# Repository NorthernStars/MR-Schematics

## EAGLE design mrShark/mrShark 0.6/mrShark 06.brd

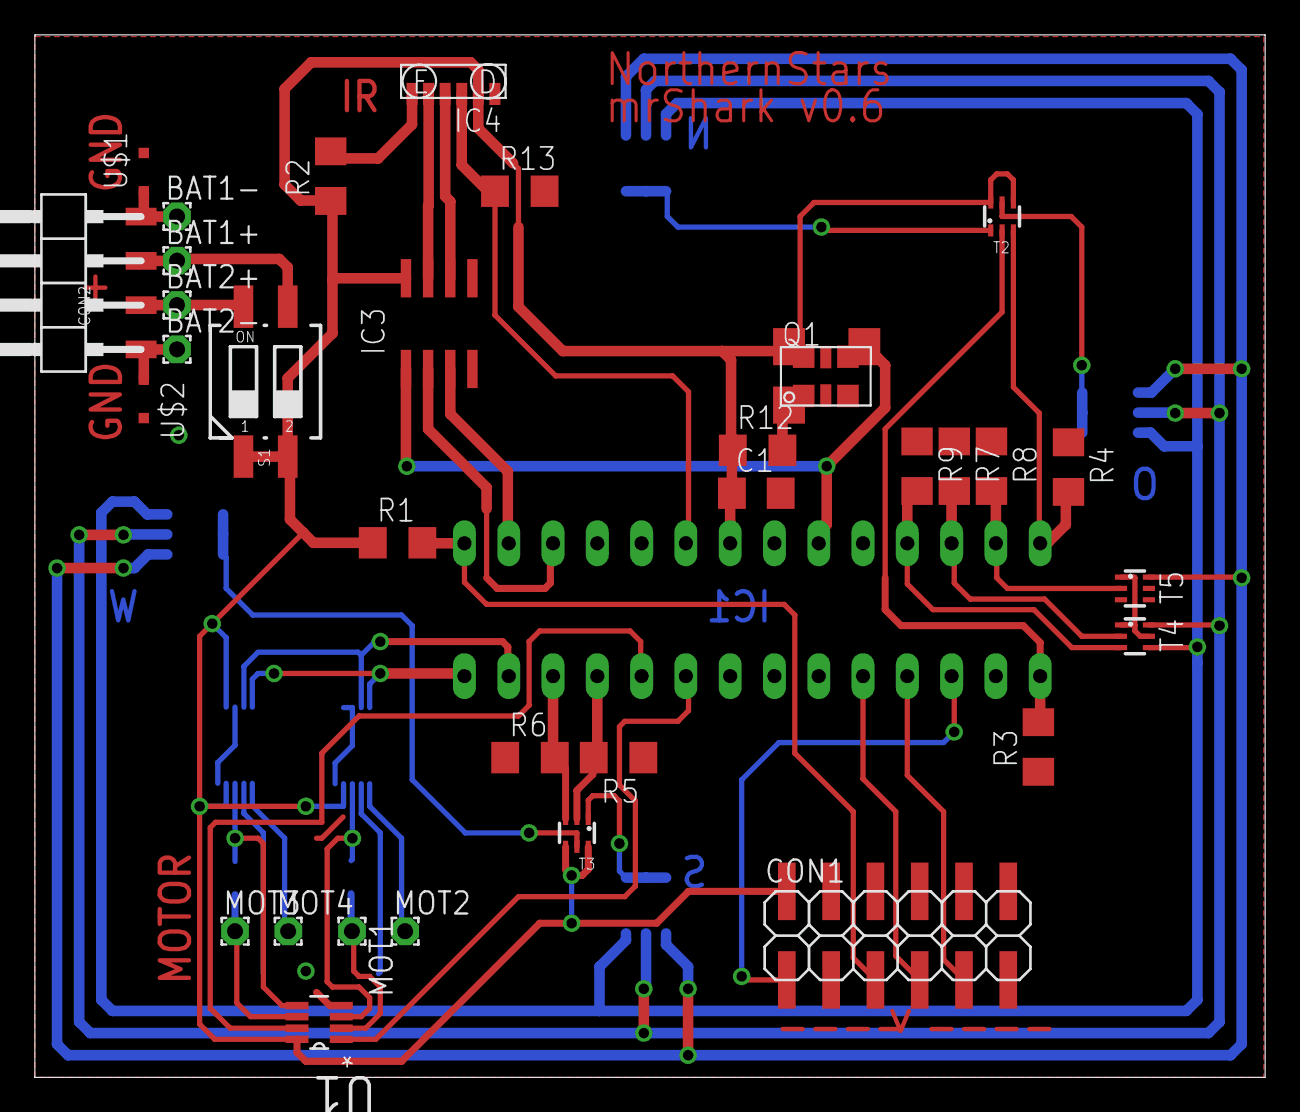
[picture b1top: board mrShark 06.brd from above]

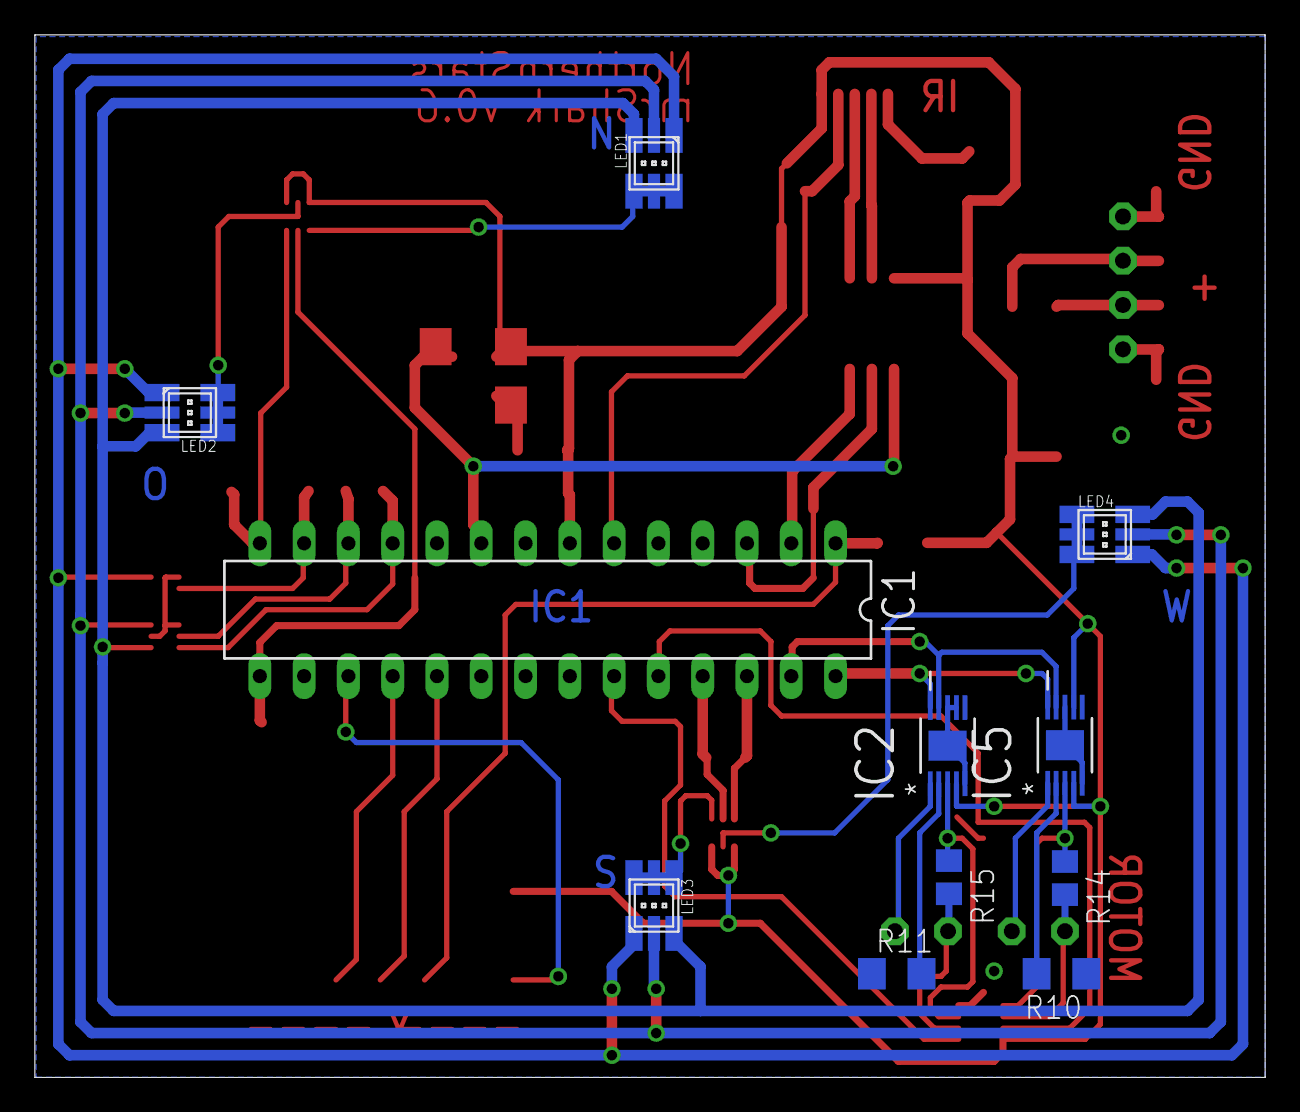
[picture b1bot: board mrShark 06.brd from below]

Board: 2 copper layers, 70.6 x 59.8 mm, 44 parts (11 on the bottom side), 44 nets.

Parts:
BAT1+, BAT1-, BAT2+, BAT2-: 1,6/0,9
C1: 100n; C1206
CON1: 2X06SMD
CON2: 1X04SMD/90
IC1: MEGA48/88/168-PU; DIL28-3
IC2, IC5: DRV8830DGQRMSOP; SOP65P640X110-15N
IC3: TIR1000PSR; SO-08
IC4: TFBS4711TR1; TFBS4711
LED1, LED2, LED3, LED4: ASMT-YTD2-0BB02; PLCC6K
MOT1, MOT2, MOT3, MOT4: 1,6/0,9
Q1: ASFLM1-1.8432MHZ-L-C-T; HC536
R1, R3, R4, R5, R6, R7, R8, R9, R12, R13: 1k; R1206
R2: 27R; R1206
R10, R11: 0.95R; R1206
R14, R15: 0R2; R0805
S1: MCEMR-02-T; CTS-219-02
T2, T3: UMX3NTR; SOT363_INFINEON
T4, T5: UMX3NTR-SOT363; SOT363_INFINEON
U1: OPA2348AIDCNTG4; SOT65P280X145-8N
U$1, U$2: PMEG2010EAR; SOD323-R

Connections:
BAT1+: BAT1+.1, CON2.3, S1.3
BAT1-: BAT1-.1, CON2.4, U$1.C
BAT2+: BAT2+.1, CON2.2, S1.4
BAT2-: BAT2-.1, CON2.1, U$2.C
CLK: IC1.9, IC3.1, Q1.3
COLOR_B: LED1.1, LED2.1, LED3.1, LED4.1, T5.6
COLOR_G: LED1.2, LED2.2, LED3.2, LED4.2, T4.6
COLOR_R: LED1.3, LED2.3, LED3.3, LED4.3, T4.4
GND: C1.2, CON1.4, CON1.6, CON1.8, CON1.10, IC1.8, IC1.22, IC2.5, IC2.7, IC2.8, IC2.11, IC3.4, IC3.5, IC4.6, IC5.5, IC5.8, IC5.11, Q1.2, R3.1, R4.1, R5.1, R6.1, R7.1, R8.1, R9.1, R10.1, R11.1, R13.2, T4.1, T4.5, T5.1, U1.4, U$1.A, U$2.A
IRDA: IC4.1, R2.2
IR_SD: IC1.6, IC4.4, R13.1
ISENS_MOTL: IC1.23, U1.1
ISENS_MOTR: IC1.24, U1.7
LED1: IC1.15, R3.2, T2.2
LED1+: LED1.4, LED1.5, LED1.6, T2.1
LED2: IC1.14, R4.2, T2.3
LED2+: LED2.4, LED2.5, LED2.6, T2.5
LED3: IC1.25, R5.2, T3.2
LED3+: LED3.4, LED3.5, LED3.6, T3.1
LED4: IC1.26, R6.2, T3.3
LED4+: LED4.4, LED4.5, LED4.6, T3.5
LED_B: IC1.13, R8.2, T5.2
LED_G: IC1.12, R7.2, T4.2
LED_R: IC1.11, R9.2, T4.3
MISO: CON1.9, IC1.18
MOSI: CON1.1, IC1.17
unnamed: IC5.1, MOT4.1
unnamed: Q1.1, R12.2
unnamed: IC5.2, R10.2
unnamed: IC2.2, R11.2
unnamed: IC2.1, MOT2.1
RESET: CON1.5, IC1.1, R1.2
RXD: IC1.2, IC3.3
RXIR: IC3.6, IC4.3
SCK: CON1.7, IC1.19
SCL: IC1.28, IC2.10, IC5.10
SDA: IC1.27, IC2.9, IC5.9
SENS_MOTL1: IC2.3, R15.1, U1.3
SENS_MOTL2: MOT1.1, R15.2, U1.2
SENS_MOTR1: IC5.3, R14.1, U1.5
SENS_MOTR2: MOT3.1, R14.2, U1.6
TXD: IC1.3, IC3.2
TXIR: IC3.7, IC4.2
VCC: C1.1, CON1.2, IC1.7, IC1.20, IC1.21, IC2.4, IC3.8, IC4.5, IC5.4, IC5.7, Q1.4, R1.1, R2.1, R12.1, S1.1, S1.2, T2.4, T2.6, T3.4, T3.6, U1.8

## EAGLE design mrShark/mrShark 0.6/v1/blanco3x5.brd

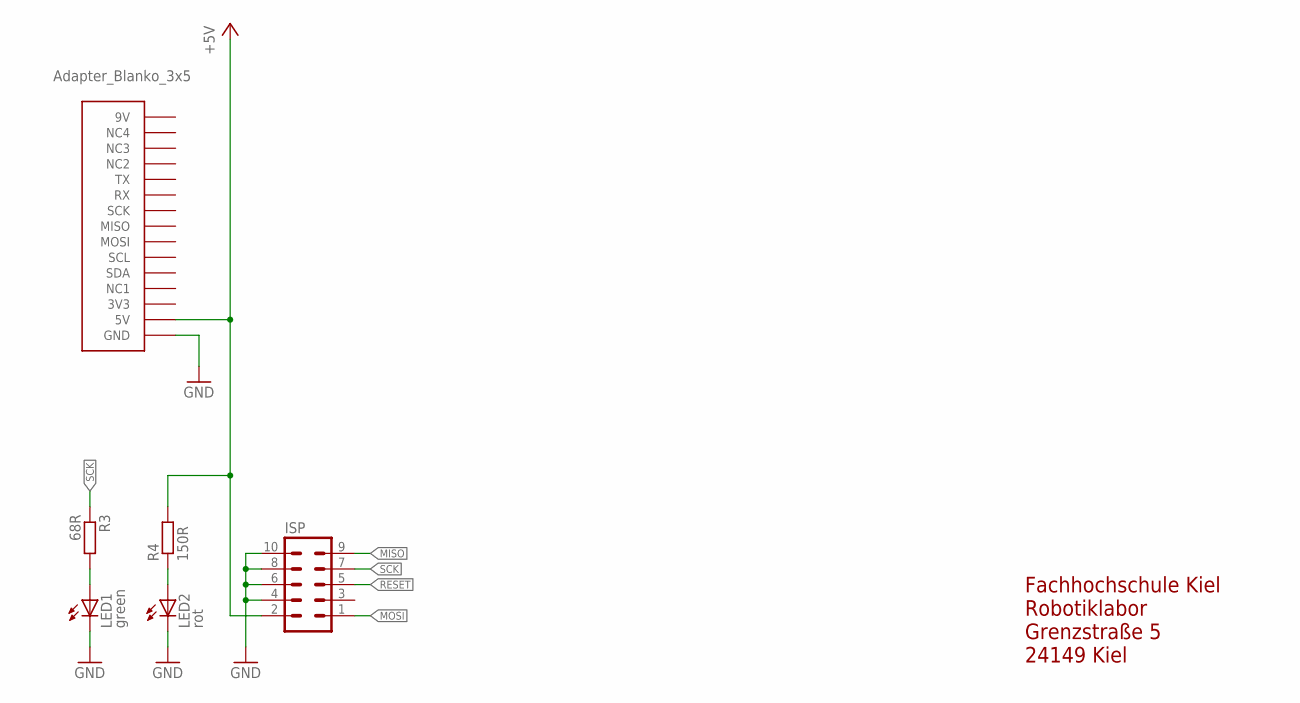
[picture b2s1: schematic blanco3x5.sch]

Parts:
ISP: ML10L
LED1: green; CHIP-LED0805
LED2: rot; CHIP-LED0805
R3: 68R; R0805W
R4: 150R; R0805W
U$1: ADAPTER_BLANKO_3X5B2; ADAPTER_BLANKO_3X5_B2

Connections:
+5V: ISP.2, R4.2, U$1.5V, U$1.5V_1 (5V)
GND: ISP.4, ISP.6, ISP.8, ISP.10, LED1.C, LED2.C, U$1.GND, U$1.GND1 (GND), U$1.GND2 (GND), U$1.GND3 (GND)
MISO: ISP.9
MOSI: ISP.1
unnamed: LED1.A, R3.2
unnamed: LED2.A, R4.1
RESET: ISP.5
SCK: ISP.7, R3.1

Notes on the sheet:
Fachhochschule Kiel Robotiklabor Grenzstraße 5 24149 Kiel

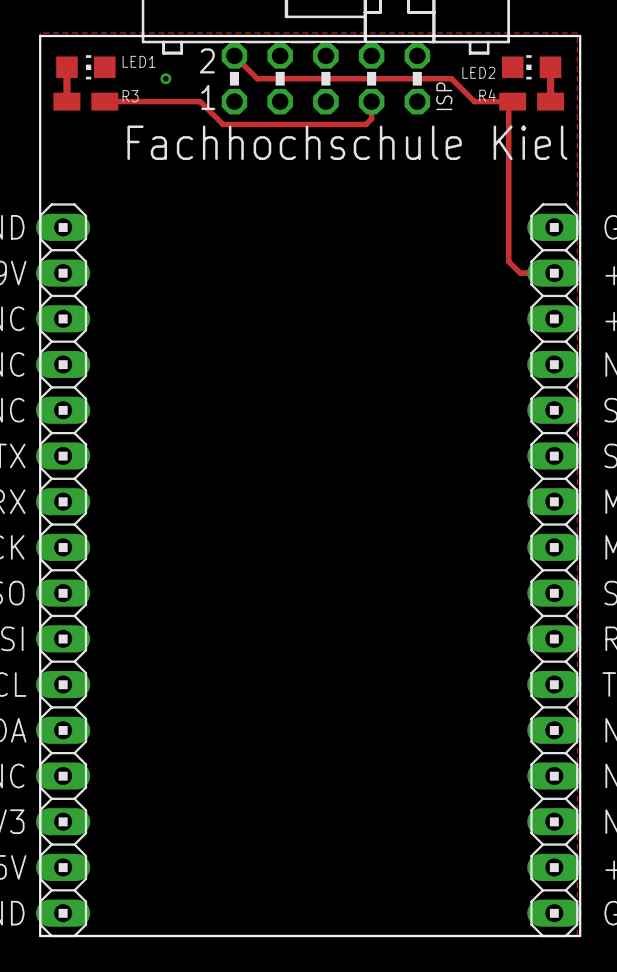
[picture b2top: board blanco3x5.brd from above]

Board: 2 copper layers, 30.0 x 50.0 mm, 6 parts (0 on the bottom side), 5 nets.

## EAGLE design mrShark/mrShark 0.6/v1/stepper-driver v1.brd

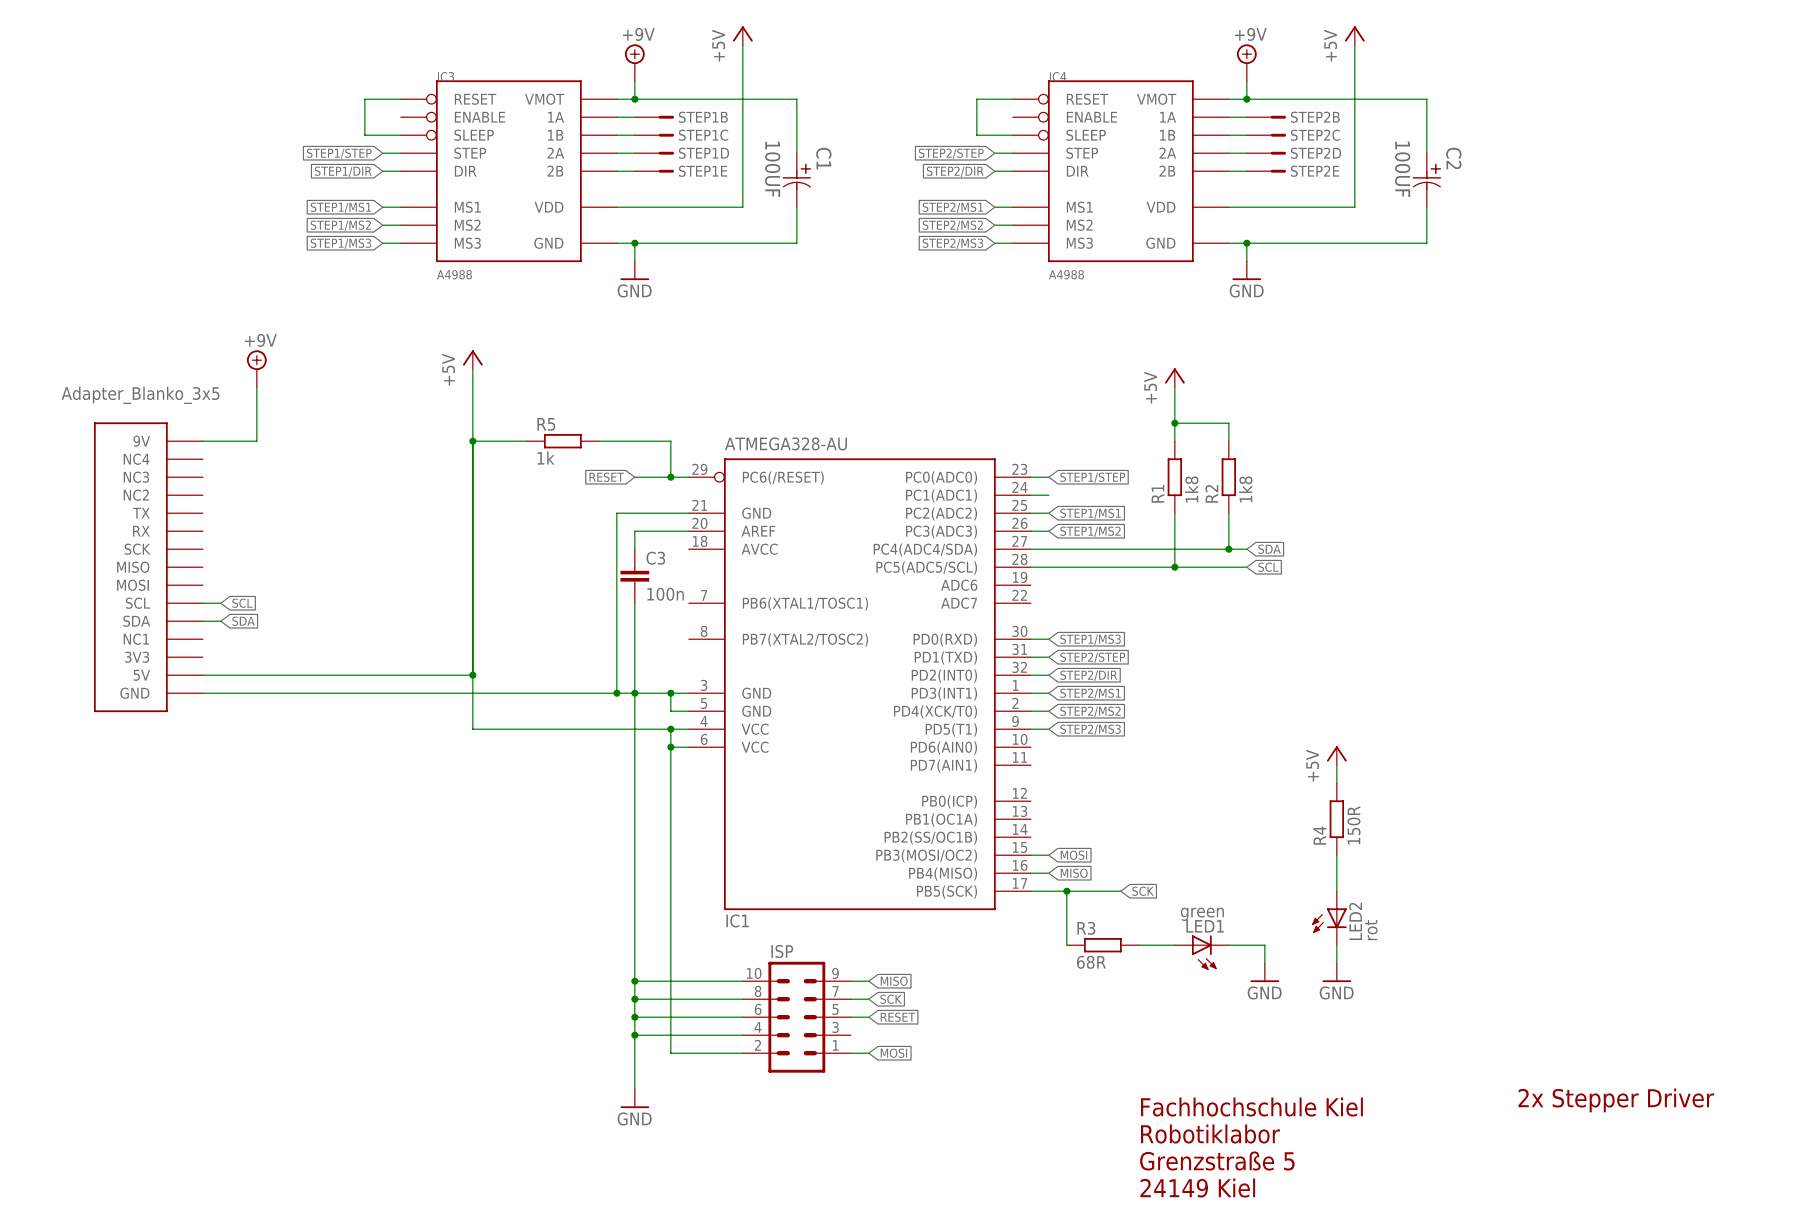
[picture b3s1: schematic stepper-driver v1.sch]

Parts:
ADAPTER: ADAPTER_BLANKO_3X5B2; ADAPTER_BLANKO_3X5_B2
C1, C2: 100UF; CAPAE660X610N
C3: 100n; C0805K
IC1: ATMEGA328-AU; TQFP32-08
IC3, IC4: A4988; A4988SHIELD-SMD
ISP: ML10L
LED1: green; CHIP-LED0805
LED2: rot; CHIP-LED0805
R1, R2: 1k8; R0805W
R3: 68R; R0805W
R4: 150R; R0805W
R5: 1k; R0805W
STEP1, STEP2: B5B-XH-A

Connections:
+5V: ADAPTER.5V, ADAPTER.5V_1 (5V), IC1.4 (VCC), IC1.6 (VCC), IC3.VDD, IC4.VDD, ISP.2, R1.2, R2.2, R4.2, R5.1
+9V: ADAPTER.9V, ADAPTER.9V_1 (9V), C1.1, C2.1, IC3.VMOT, IC4.VMOT
AVCC: IC1.18 (AVCC)
GND: ADAPTER.GND, ADAPTER.GND1 (GND), ADAPTER.GND2 (GND), ADAPTER.GND3 (GND), C1.2, C2.2, C3.2, IC1.3 (GND), IC1.5 (GND), IC1.21 (GND), IC3.GND, IC3.GND1 (GND), IC4.GND, IC4.GND1 (GND), ISP.4, ISP.6, ISP.8, ISP.10, LED1.C, LED2.C
MISO: IC1.16 (PB4(MISO)), ISP.9
MOSI: IC1.15 (PB3(MOSI/OC2)), ISP.1
unnamed: C3.1, IC1.20 (AREF)
unnamed: LED1.A, R3.2
unnamed: LED2.A, R4.1
unnamed: IC3.2B, STEP1.5
unnamed: IC3.2A, STEP1.4
unnamed: IC3.1B, STEP1.3
unnamed: IC3.1A, STEP1.2
unnamed: IC4.1A, STEP2.2
unnamed: IC4.1B, STEP2.3
unnamed: IC4.2A, STEP2.4
unnamed: IC4.2B, STEP2.5
RESET: IC1.29 (PC6(/RESET)), ISP.5, R5.2
SCK: IC1.17 (PB5(SCK)), ISP.7, R3.1
SCL: ADAPTER.SCL, ADAPTER.SCL_1 (SCL), IC1.28 (PC5(ADC5/SCL)), R1.1
SDA: ADAPTER.SDA, ADAPTER.SDA_1 (SDA), IC1.27 (PC4(ADC4/SDA)), R2.1
STEP1/DIR: IC1.24 (PC1(ADC1)), IC3.DIR
STEP1/MS1: IC1.25 (PC2(ADC2)), IC3.MS1
STEP1/MS2: IC1.26 (PC3(ADC3)), IC3.MS2
STEP1/MS3: IC1.30 (PD0(RXD)), IC3.MS3
STEP1/RESET: IC3.RESET, IC3.SLEEP
STEP1/STEP: IC1.23 (PC0(ADC0)), IC3.STEP
STEP2/DIR: IC1.32 (PD2(INT0)), IC4.DIR
STEP2/MS1: IC1.1 (PD3(INT1)), IC4.MS1
STEP2/MS2: IC1.2 (PD4(XCK/T0)), IC4.MS2
STEP2/MS3: IC1.9 (PD5(T1)), IC4.MS3
STEP2/RESET: IC4.RESET, IC4.SLEEP
STEP2/STEP: IC1.31 (PD1(TXD)), IC4.STEP

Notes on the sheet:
Fachhochschule Kiel Robotiklabor Grenzstraße 5 24149 Kiel
2x Stepper Driver

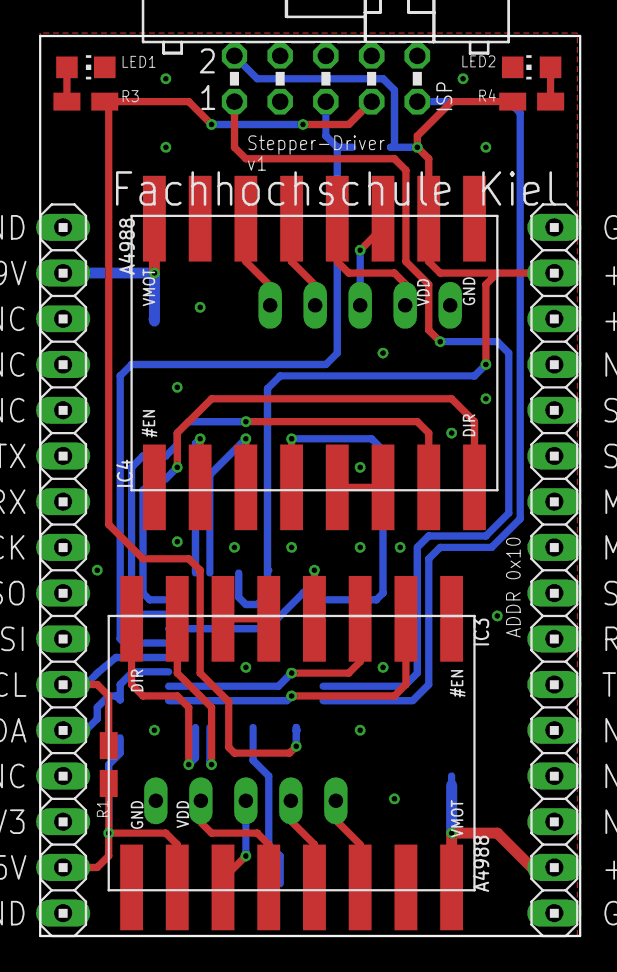
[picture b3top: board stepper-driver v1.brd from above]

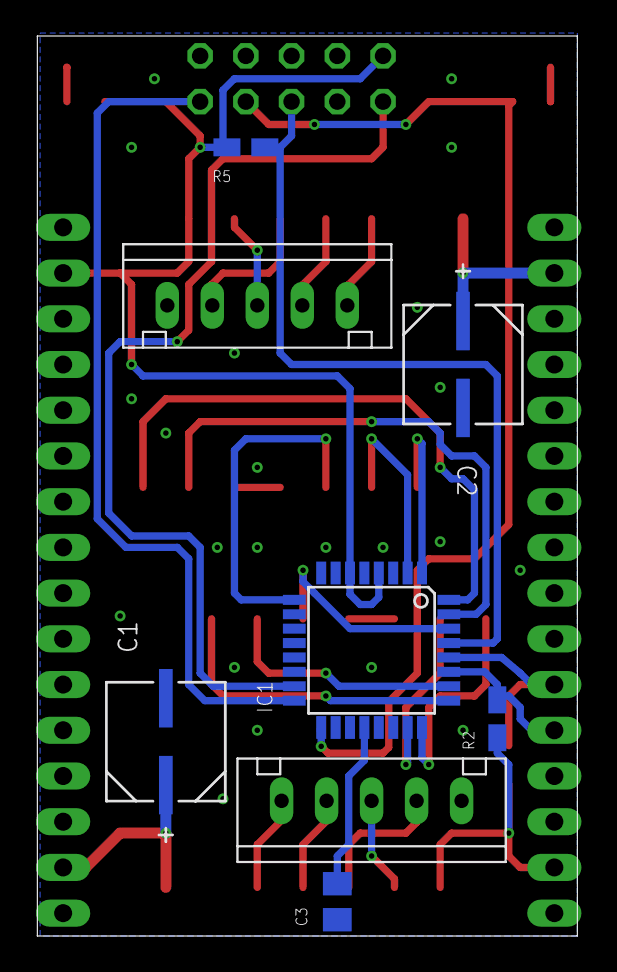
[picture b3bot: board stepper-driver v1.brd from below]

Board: 2 copper layers, 30.0 x 50.0 mm, 17 parts (8 on the bottom side), 32 nets.

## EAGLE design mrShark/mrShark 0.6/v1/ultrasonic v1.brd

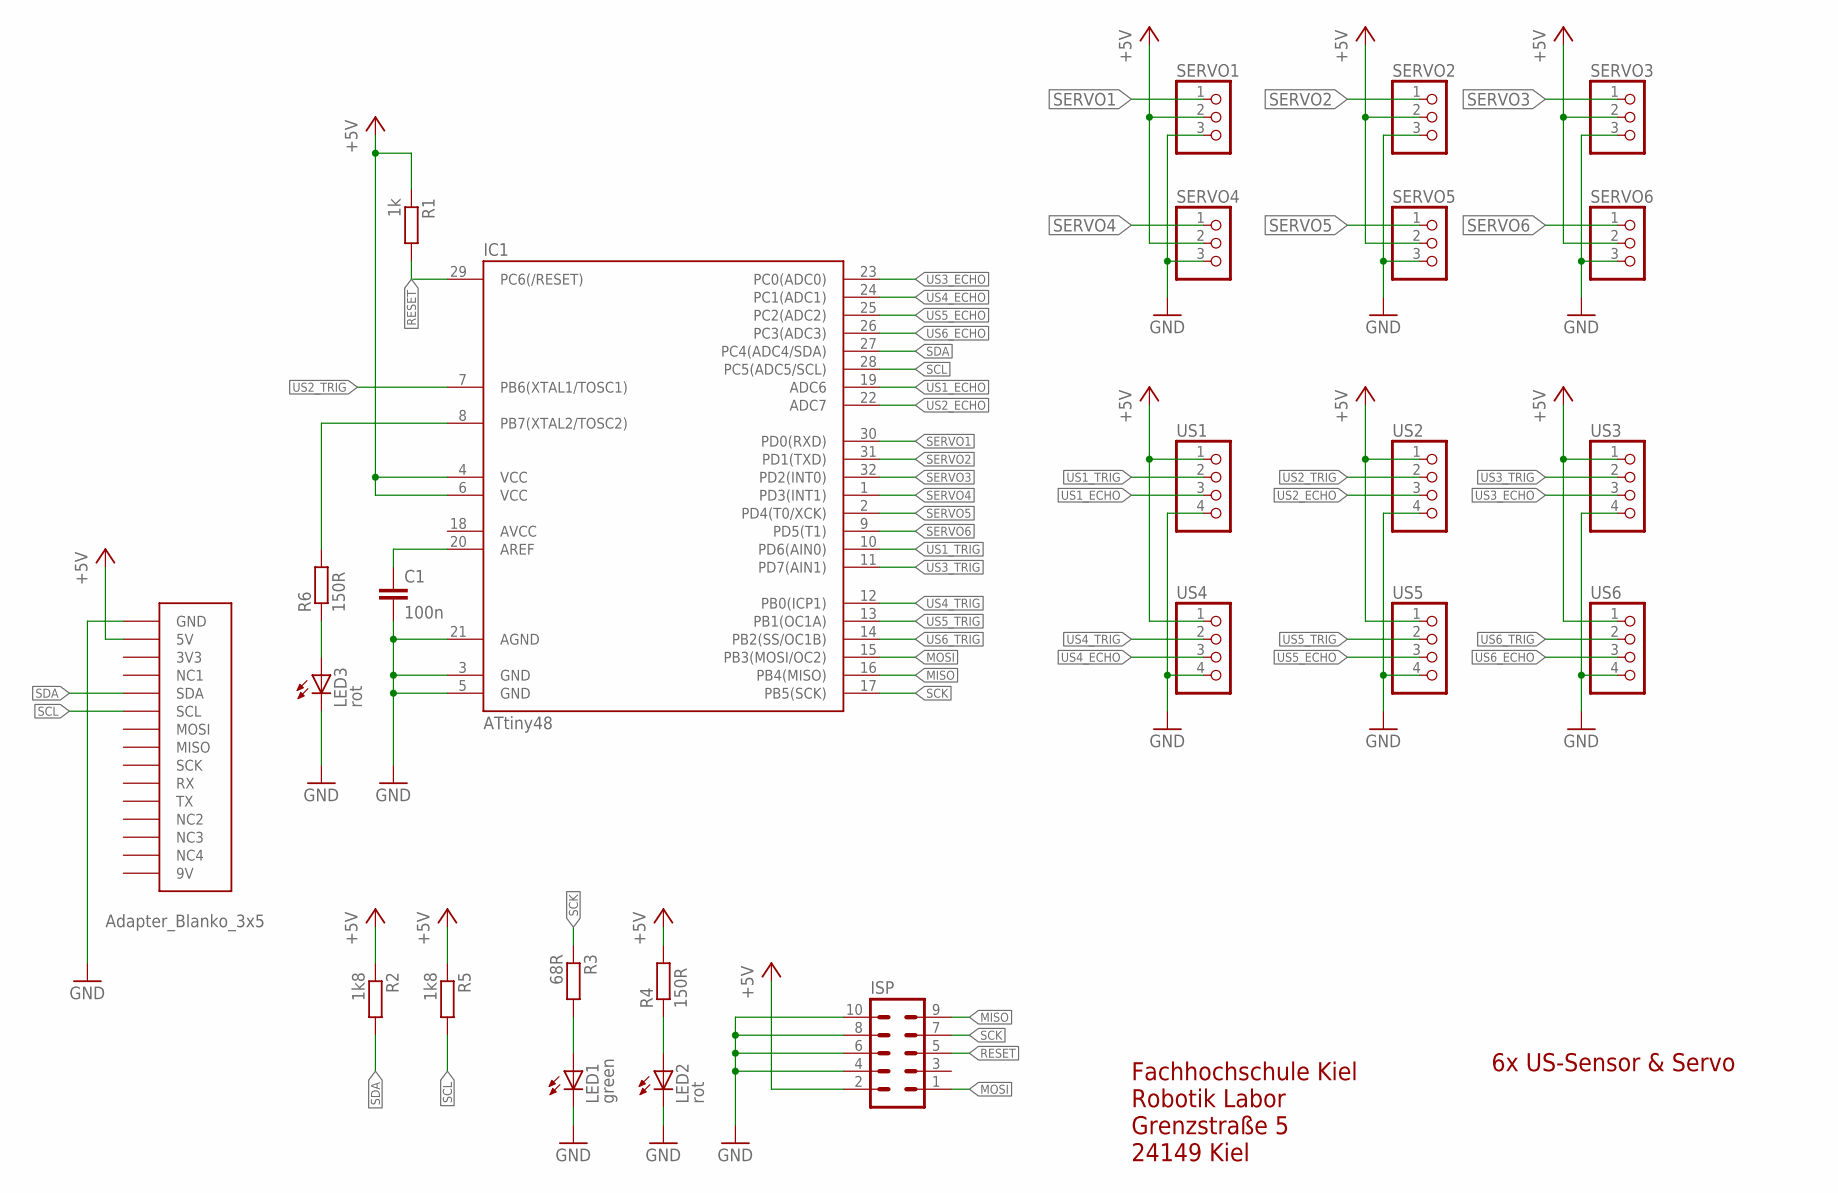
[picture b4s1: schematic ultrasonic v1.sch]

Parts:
C1: 100n; C0805
IC1: ATtiny48; TQFP32-08
ISP: ML10L
LED1: green; CHIP-LED0805
LED2, LED3: rot; CHIP-LED0805
R1: 1k; R0805W
R2, R5: 1k8; R0805W
R3: 68R; R0805W
R4, R6: 150R; R0805W
SERVO1, SERVO2, SERVO3, SERVO4, SERVO5, SERVO6: PINHD-1X3; 1X03
U$1: ADAPTER_BLANKO_3X5B2; ADAPTER_BLANKO_3X5_B2
US1, US2, US3, US4, US5, US6: PINHD-1X4; 1X04

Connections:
+5V: IC1.4 (VCC), IC1.6 (VCC), ISP.2, R1.1, R2.1, R4.2, R5.1, SERVO1.2, SERVO2.2, SERVO3.2, SERVO4.2, SERVO5.2, SERVO6.2, U$1.5V, U$1.5V_1 (5V), US1.1, US2.1, US3.1, US4.1, US5.1, US6.1
GND: C1.2, IC1.3 (GND), IC1.5 (GND), IC1.21 (AGND), ISP.4, ISP.6, ISP.8, ISP.10, LED1.C, LED2.C, LED3.C, SERVO1.3, SERVO2.3, SERVO3.3, SERVO4.3, SERVO5.3, SERVO6.3, U$1.GND, U$1.GND1 (GND), U$1.GND2 (GND), U$1.GND3 (GND), US1.4, US2.4, US3.4, US4.4, US5.4, US6.4
MISO: IC1.16 (PB4(MISO)), ISP.9
MOSI: IC1.15 (PB3(MOSI/OC2)), ISP.1
unnamed: IC1.8 (PB7(XTAL2/TOSC2)), R6.2
unnamed: LED3.A, R6.1
unnamed: LED1.A, R3.2
unnamed: LED2.A, R4.1
unnamed: C1.1, IC1.20 (AREF)
RESET: IC1.29 (PC6(/RESET)), ISP.5, R1.2
SCK: IC1.17 (PB5(SCK)), ISP.7, R3.1
SCL: IC1.28 (PC5(ADC5/SCL)), R5.2, U$1.SCL, U$1.SCL_1 (SCL)
SDA: IC1.27 (PC4(ADC4/SDA)), R2.2, U$1.SDA, U$1.SDA_1 (SDA)
SERVO1: IC1.30 (PD0(RXD)), SERVO1.1
SERVO2: IC1.31 (PD1(TXD)), SERVO2.1
SERVO3: IC1.32 (PD2(INT0)), SERVO3.1
SERVO4: IC1.1 (PD3(INT1)), SERVO4.1
SERVO5: IC1.2 (PD4(T0/XCK)), SERVO5.1
SERVO6: IC1.9 (PD5(T1)), SERVO6.1
US1_ECHO: IC1.19 (ADC6), US1.3
US1_TRIG: IC1.10 (PD6(AIN0)), US1.2
US2_ECHO: IC1.22 (ADC7), US2.3
US2_TRIG: IC1.7 (PB6(XTAL1/TOSC1)), US2.2
US3_ECHO: IC1.23 (PC0(ADC0)), US3.3
US3_TRIG: IC1.11 (PD7(AIN1)), US3.2
US4_ECHO: IC1.24 (PC1(ADC1)), US4.3
US4_TRIG: IC1.12 (PB0(ICP1)), US4.2
US5_ECHO: IC1.25 (PC2(ADC2)), US5.3
US5_TRIG: IC1.13 (PB1(OC1A)), US5.2
US6_ECHO: IC1.26 (PC3(ADC3)), US6.3
US6_TRIG: IC1.14 (PB2(SS/OC1B)), US6.2

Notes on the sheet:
Fachhochschule Kiel Robotik Labor Grenzstraße 5 24149 Kiel
6x US-Sensor & Servo

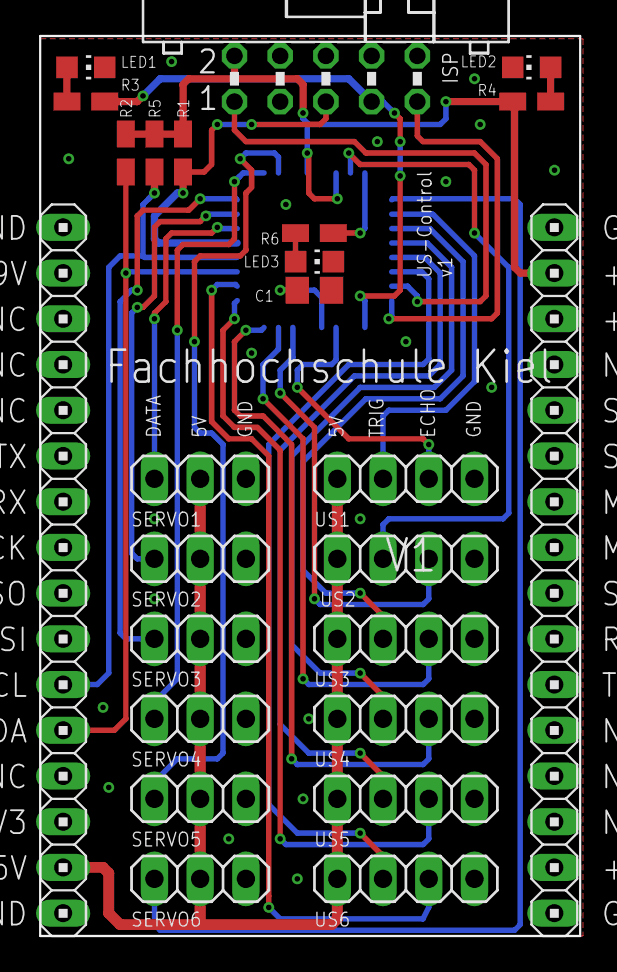
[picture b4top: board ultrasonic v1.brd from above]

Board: 2 copper layers, 30.0 x 50.0 mm, 25 parts (1 on the bottom side), 31 nets.

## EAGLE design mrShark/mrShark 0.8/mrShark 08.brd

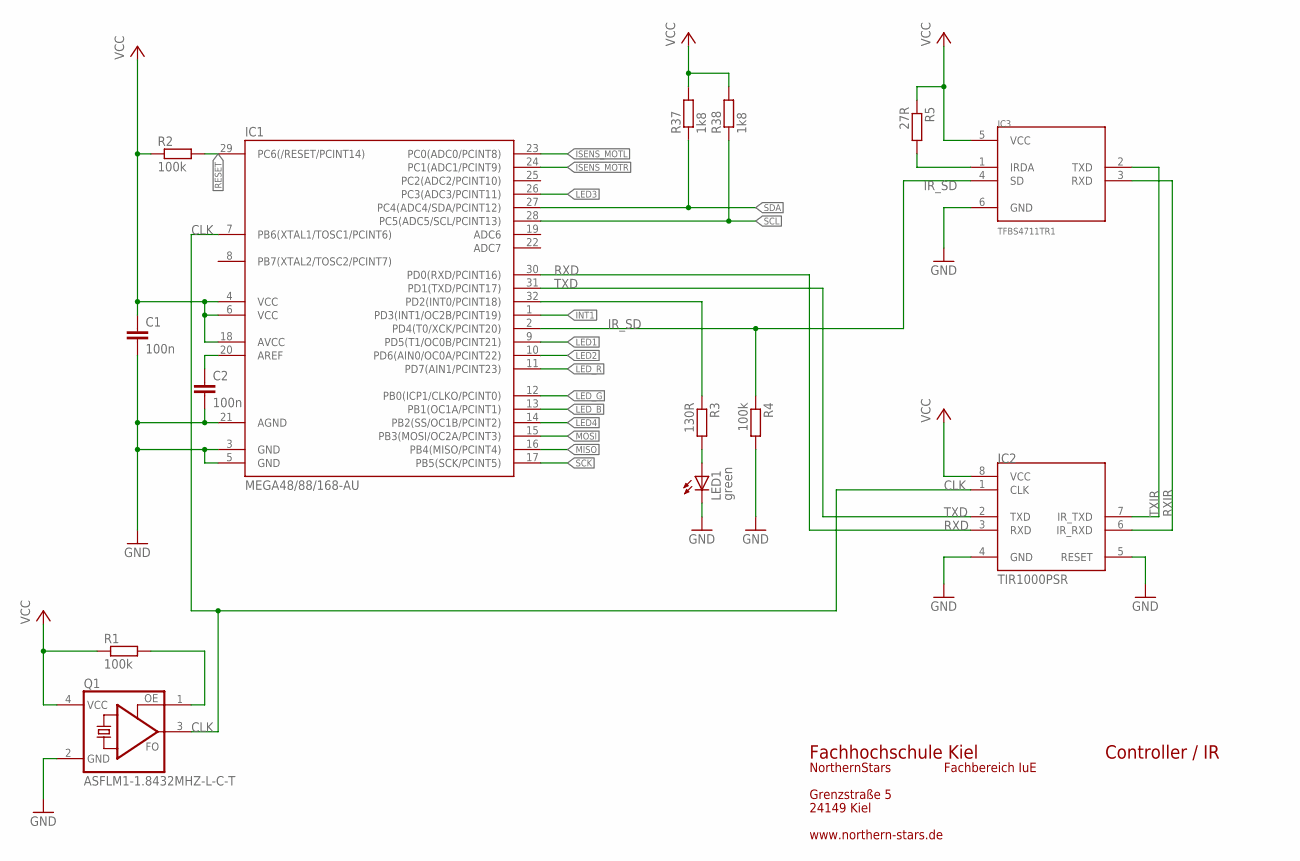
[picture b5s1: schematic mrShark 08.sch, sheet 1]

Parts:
C1, C2: 100n; C0805
IC1: MEGA48/88/168-AU; TQFP32-08
IC2: TIR1000PSR; SO-08
IC3: TFBS4711TR1; TFBS4711
LED1: green; CHIPLED_1206
Q1: ASFLM1-1.8432MHZ-L-C-T; HC736
R1, R2, R4: 100k; R1206
R3: 130R; R1206
R5: 27R; R1206
R37, R38: 1k8; R1206

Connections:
CLK: IC1.7 (PB6(XTAL1/TOSC1/PCINT6)), IC2.1 (CLK), Q1.3 (FO)
GND: C1.2, C2.2, IC1.3 (GND), IC1.5 (GND), IC1.21 (AGND), IC2.4 (GND), IC2.5 (RESET), IC3.6 (GND), LED1.C, Q1.2 (GND), R4.2; also elsewhere on the board
INT1: IC1.1 (PD3(INT1/OC2B/PCINT19))
IRDA: IC3.1 (IRDA), R5.2
IR_SD: IC1.2 (PD4(T0/XCK/PCINT20)), IC3.4 (SD), R4.1
ISENS_MOTL: IC1.23 (PC0(ADC0/PCINT8)); also elsewhere on the board
ISENS_MOTR: IC1.24 (PC1(ADC1/PCINT9)); also elsewhere on the board
LED1: IC1.9 (PD5(T1/OC0B/PCINT21)); also elsewhere on the board
LED2: IC1.10 (PD6(AIN0/OC0A/PCINT22)); also elsewhere on the board
LED3: IC1.26 (PC3(ADC3/PCINT11)); also elsewhere on the board
LED4: IC1.14 (PB2(SS/OC1B/PCINT2)); also elsewhere on the board
LED_B: IC1.13 (PB1(OC1A/PCINT1)); also elsewhere on the board
LED_G: IC1.12 (PB0(ICP1/CLKO/PCINT0)); also elsewhere on the board
LED_R: IC1.11 (PD7(AIN1/PCINT23)); also elsewhere on the board
MISO: IC1.16 (PB4(MISO/PCINT4)); also elsewhere on the board
MOSI: IC1.15 (PB3(MOSI/OC2A/PCINT3)); also elsewhere on the board
unnamed: Q1.1 (OE), R1.2
unnamed: C2.1, IC1.20 (AREF)
unnamed: IC1.32 (PD2(INT0/PCINT18)), R3.1
unnamed: LED1.A, R3.2
RESET: IC1.29 (PC6(/RESET/PCINT14)), R2.2; also elsewhere on the board
RXD: IC1.30 (PD0(RXD/PCINT16)), IC2.3 (RXD)
RXIR: IC2.6 (IR_RXD), IC3.3 (RXD)
SCK: IC1.17 (PB5(SCK/PCINT5)); also elsewhere on the board
SCL: IC1.28 (PC5(ADC5/SCL/PCINT13)), R38.1; also elsewhere on the board
SDA: IC1.27 (PC4(ADC4/SDA/PCINT12)), R37.1; also elsewhere on the board
TXD: IC1.31 (PD1(TXD/PCINT17)), IC2.2 (TXD)
TXIR: IC2.7 (IR_TXD), IC3.2 (TXD)
VCC: C1.1, IC1.4 (VCC), IC1.6 (VCC), IC1.18 (AVCC), IC2.8 (VCC), IC3.5 (VCC), Q1.4 (VCC), R1.1, R2.1, R5.1, R37.2, R38.2; also elsewhere on the board

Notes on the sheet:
Fachhochschule Kiel
Grenzstraße 5
24149 Kiel
NorthernStars
Fachbereich IuE
www.northern-stars.de
Controller / IR

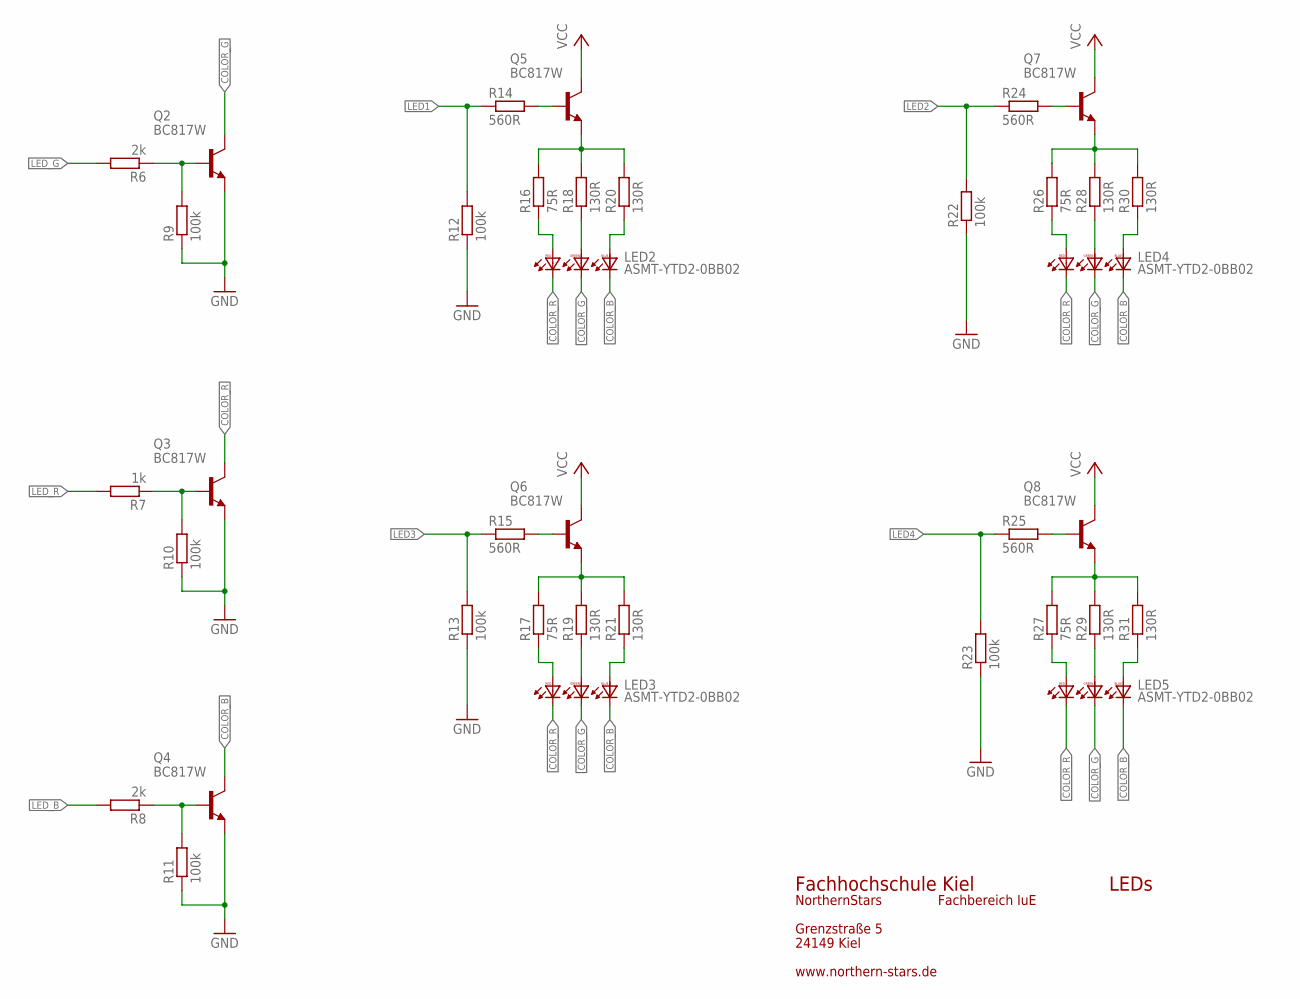
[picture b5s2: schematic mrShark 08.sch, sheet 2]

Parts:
LED2, LED3, LED4, LED5: ASMT-YTD2-0BB02; PLCC6K
Q2, Q3, Q4, Q5, Q6, Q7, Q8: BC817W; SOT323-BEC
R6, R8: 2k; R1206
R7: 1k; R1206
R9, R10, R11, R12, R13, R22, R23: 100k; R1206
R14, R15, R24, R25: 560R; R1206
R16, R17, R26, R27: 75R; R1206
R18, R19, R20, R21, R28, R29, R30, R31: 130R; R1206

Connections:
COLOR_B: LED2.1 (BC), LED3.1 (BC), LED4.1 (BC), LED5.1 (BC), Q4.C
COLOR_G: LED2.2 (GC), LED3.2 (GC), LED4.2 (GC), LED5.2 (GC), Q2.C
COLOR_R: LED2.3 (RC), LED3.3 (RC), LED4.3 (RC), LED5.3 (RC), Q3.C
GND: Q2.E, Q3.E, Q4.E, R9.1, R10.1, R11.1, R12.1, R13.1, R22.1, R23.1; also elsewhere on the board
LED1: R12.2, R14.1; also elsewhere on the board
LED2: R22.2, R24.1; also elsewhere on the board
LED3: R13.2, R15.1; also elsewhere on the board
LED4: R23.2, R25.1; also elsewhere on the board
LED_B: R8.2; also elsewhere on the board
LED_G: R6.2; also elsewhere on the board
LED_R: R7.2; also elsewhere on the board
unnamed: LED2.4 (RA), R16.1
unnamed: LED2.5 (GA), R18.1
unnamed: Q5.E, R16.2, R18.2, R20.2
unnamed: LED4.4 (RA), R26.1
unnamed: LED4.5 (GA), R28.1
unnamed: LED4.6 (BA), R30.1
unnamed: Q7.E, R26.2, R28.2, R30.2
unnamed: Q6.E, R17.2, R19.2, R21.2
unnamed: LED3.4 (RA), R17.1
unnamed: LED3.5 (GA), R19.1
unnamed: LED3.6 (BA), R21.1
unnamed: Q8.E, R27.2, R29.2, R31.2
unnamed: Q6.B, R15.2
unnamed: LED5.4 (RA), R27.1
unnamed: LED5.5 (GA), R29.1
unnamed: LED5.6 (BA), R31.1
unnamed: Q8.B, R25.2
unnamed: Q7.B, R24.2
unnamed: Q5.B, R14.2
unnamed: LED2.6 (BA), R20.1
VCC: Q5.C, Q6.C, Q7.C, Q8.C; also elsewhere on the board
X1: Q4.B, R8.1, R11.2
X2: Q3.B, R7.1, R10.2
X3: Q2.B, R6.1, R9.2

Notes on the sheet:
LEDs
Fachhochschule Kiel
Grenzstraße 5
24149 Kiel
NorthernStars
Fachbereich IuE
www.northern-stars.de

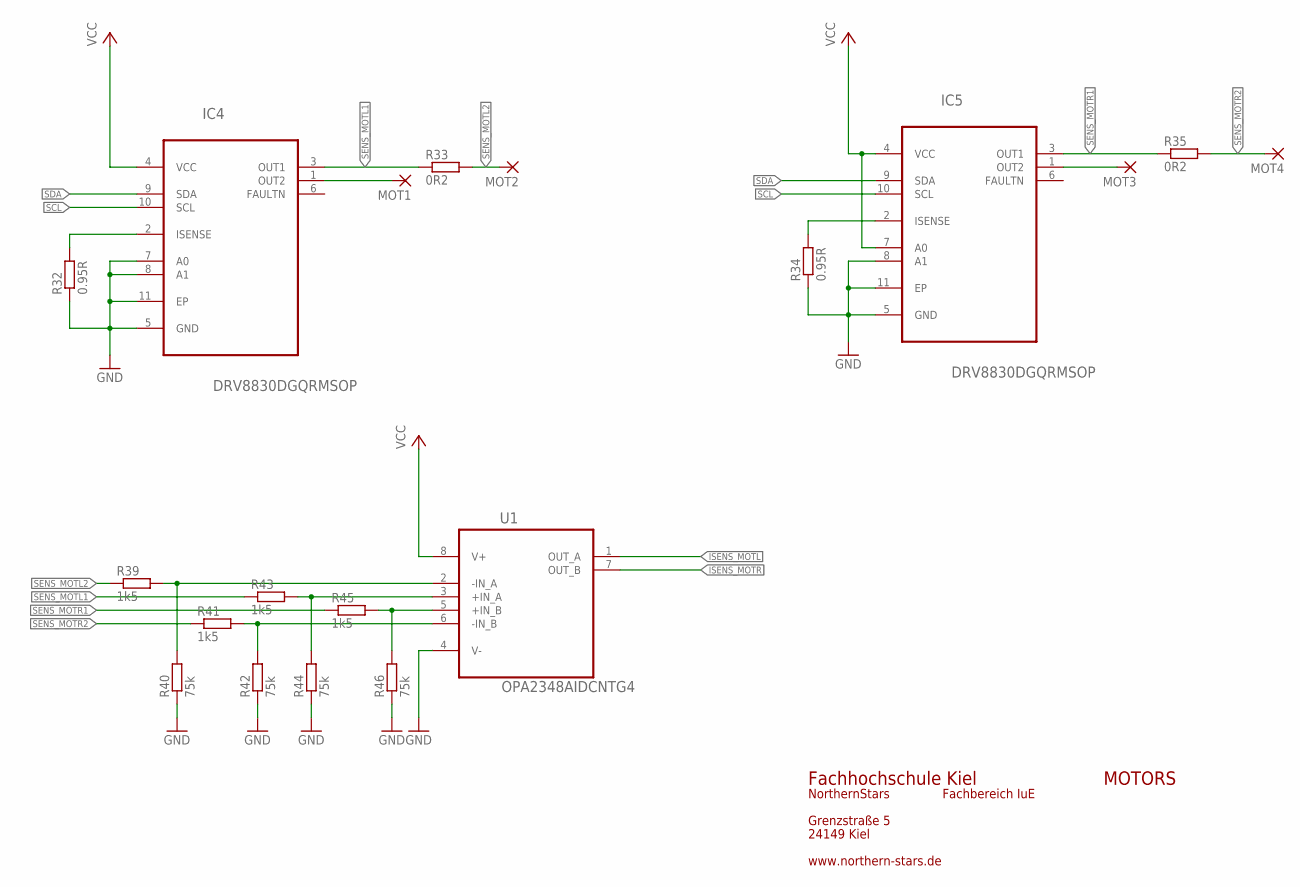
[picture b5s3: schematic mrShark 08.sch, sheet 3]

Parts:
IC4, IC5: DRV8830DGQRMSOP; SOP65P640X110-15N
MOT1, MOT2, MOT3, MOT4: 1,6/0,9
R32, R34: 0.95R; R1206
R33, R35: 0R2; R0805
R39, R41, R43, R45: 1k5; R1206
R40, R42, R44, R46: 75k; R1206
U1: OPA2348AIDCNTG4; SOT65P280X145-8N

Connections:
GND: IC4.5 (GND), IC4.7 (A0), IC4.8 (A1), IC4.11 (EP), IC5.5 (GND), IC5.8 (A1), IC5.11 (EP), R32.1, R34.1, R40.1, R42.1, R44.1, R46.1, U1.4 (V-); also elsewhere on the board
ISENS_MOTL: U1.1 (OUT_A); also elsewhere on the board
ISENS_MOTR: U1.7 (OUT_B); also elsewhere on the board
unnamed: IC4.1 (OUT2), MOT1.1
unnamed: IC4.2 (ISENSE), R32.2
unnamed: R39.2, R40.2, U1.2 (-IN_A)
unnamed: IC5.1 (OUT2), MOT3.1
unnamed: IC5.2 (ISENSE), R34.2
unnamed: R41.2, R42.2, U1.6 (-IN_B)
unnamed: R43.2, R44.2, U1.3 (+IN_A)
unnamed: R45.2, R46.2, U1.5 (+IN_B)
SCL: IC4.10 (SCL), IC5.10 (SCL); also elsewhere on the board
SDA: IC4.9 (SDA), IC5.9 (SDA); also elsewhere on the board
SENS_MOTL1: IC4.3 (OUT1), R33.1, R43.1
SENS_MOTL2: MOT2.1, R33.2, R39.1
SENS_MOTR1: IC5.3 (OUT1), R35.1, R45.1
SENS_MOTR2: MOT4.1, R35.2, R41.1
VCC: IC4.4 (VCC), IC5.4 (VCC), IC5.7 (A0), U1.8 (V+); also elsewhere on the board

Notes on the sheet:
MOTORS
Fachhochschule Kiel
Grenzstraße 5
24149 Kiel
NorthernStars
Fachbereich IuE
www.northern-stars.de
